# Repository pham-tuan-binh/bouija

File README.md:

# Bouija

A PCB business card that runs an LLM locally with an Ouija board-inspired LED layout.

Watch a video on the design of this business card [here](https://youtu.be/WC3O2cKT8Eo).

**Special thanks to NextPB for sponsoring this project. Check out their website [here](https://www.nextpcb.com?code=Build_With_Binh)**

## Overview

Bouija is a unique business card featuring an ESP32-S3 that runs a local Large Language Model. The device uses 40 individually addressable WS2812B LEDs arranged in an Ouija board pattern to visualize text generation in real-time.

## Specifications

- **PCB Dimensions**: 85mm × 54mm with 3mm corner radius
- **LEDs**: 40 WS2812B LEDs
  - 26 letters (A-Z)
  - 10 numbers (0-9)
  - 4 shortcuts: cap, slap, peace, sup
- **MCU**: ESP32-S3 with 8MB PSRAM and 16MB Flash
- **Layout**: Ouija board arrangement for cultural authenticity

## Firmware Options

### Simple Mode (`/firmware/simple`)

Hard-coded messages with LED visualization and touch interaction.

### LLM Mode (`/firmware/tinyllama`)

Local LLM text generation using [Dave Bennett's ESP32 LLM implementation](https://github.com/DaveBben/esp32-llm). Credit to Dave Bennett for the LLM core - I added the visualization and interaction layer.

## Setup

Requires ESP-IDF toolchain:

```bash
# Navigate to desired firmware directory
cd firmware/tinyllama  # or firmware/simple

# Build and flash
idf.py build
idf.py -p /dev/{DEVICE_PORT} flash
```

## Hardware

The PCB design is available in `/pcb` as a KiCad project.

## Why "Bouija"?

It's a play on "Ouija" + "Binh" (the creator's name) - because what's a business card without a little wordplay? 👻

---

_Running AI on a business card because why not?_

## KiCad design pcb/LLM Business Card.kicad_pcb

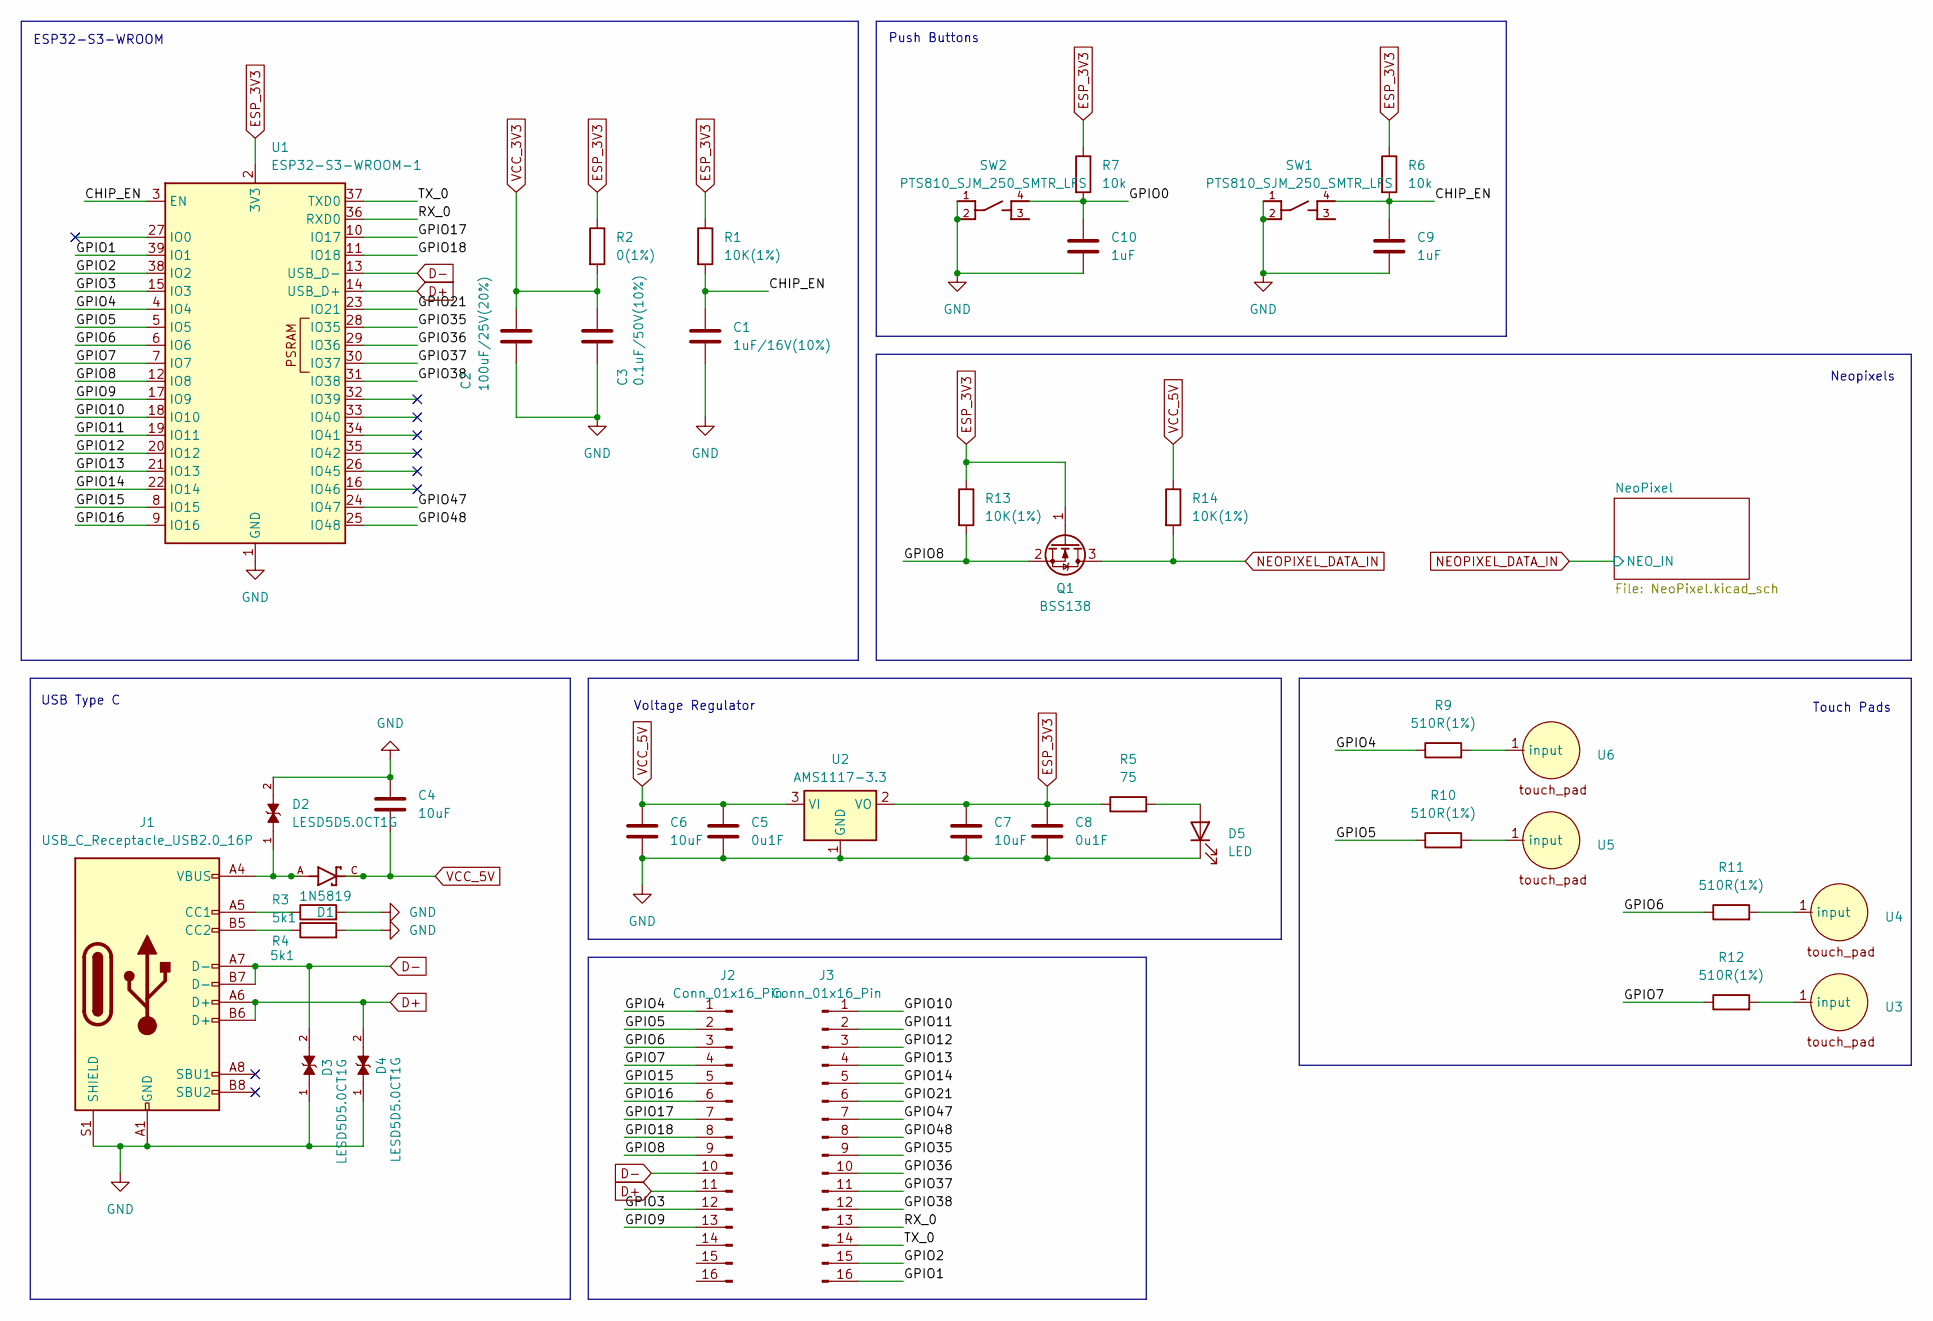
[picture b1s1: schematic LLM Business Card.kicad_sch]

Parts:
C1: 1uF/16V(10%); C_0805_2012Metric
C2: 100uF/25V(20%); C_0805_2012Metric
C3: 0.1uF/50V(10%); C_0805_2012Metric
C4, C6, C7: 10uF; C_0805_2012Metric
C5, C8: 0u1F; C_0805_2012Metric
C9, C10: 1uF; C_0805_2012Metric
D1: 1N5819; SOD3715X145N; PARTREV 18-2
D2, D3, D4: LESD5D5.0CT1G; TVS_LESD5D5.0CT1G; PARTREV O
D5: LED; LED_0402_1005Metric_Pad0.77x0.64mm_HandSolder
J1: USB_C_Receptacle_USB2.0_16P; USB_C_Receptacle_GCT_USB4105-xx-A_16P_TopMnt_Horizontal
J2, J3: Conn_01x16_Pin; PinSocket_1x16_P2.54mm_Vertical
Q1: BSS138; SOT-23
R1, R13, R14: 10K(1%); R_0402_1005Metric_Pad0.72x0.64mm_HandSolder
R2: 0(1%); R_0402_1005Metric_Pad0.72x0.64mm_HandSolder
R3, R4: 5k1; R_0402_1005Metric_Pad0.72x0.64mm_HandSolder
R5: 75; R_0402_1005Metric_Pad0.72x0.64mm_HandSolder
R6, R7: 10k; R_0402_1005Metric_Pad0.72x0.64mm_HandSolder
R9, R10, R11, R12: 510R(1%); R_0402_1005Metric_Pad0.72x0.64mm_HandSolder
SW1, SW2: PTS810_SJM_250_SMTR_LFS; SW_PTS810_SJM_250_SMTR_LFS
U1: ESP32-S3-WROOM-1
U2: AMS1117-3.3; SOT-223-3_TabPin2
U3, U4, U5, U6: TouchPad

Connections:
/CHIP_EN: C1.1, C9.1, R1.2, R6.2, SW1.4, U1.3 (EN)
/GPIO0: C10.1, R7.2, SW2.4
/GPIO1: J3.16, U1.39 (IO1)
/GPIO2: J3.15, U1.38 (IO2)
/GPIO3: J2.12, U1.15 (IO3)
/GPIO4: J2.1, R9.1, U1.4 (IO4)
/GPIO5: J2.2, R10.1, U1.5 (IO5)
/GPIO6: J2.3, R11.1, U1.6 (IO6)
/GPIO7: J2.4, R12.1, U1.7 (IO7)
/GPIO8: J2.9, Q1.2 (S), R13.2, U1.12 (IO8)
/GPIO9: J2.13, U1.17 (IO9)
/GPIO10: J3.1, U1.18 (IO10)
/GPIO11: J3.2, U1.19 (IO11)
/GPIO12: J3.3, U1.20 (IO12)
/GPIO13: J3.4, U1.21 (IO13)
/GPIO14: J3.5, U1.22 (IO14)
/GPIO15: J2.5, U1.8 (IO15)
/GPIO16: J2.6, U1.9 (IO16)
/GPIO17: J2.7, U1.10 (IO17)
/GPIO18: J2.8, U1.11 (IO18)
/GPIO21: J3.6, U1.23 (IO21)
/GPIO35: J3.9, U1.28 (IO35)
/GPIO36: J3.10, U1.29 (IO36)
/GPIO37: J3.11, U1.30 (IO37)
/GPIO38: J3.12, U1.31 (IO38)
/GPIO47: J3.7, U1.24 (IO47)
/GPIO48: J3.8, U1.25 (IO48)
/RX_0: J3.13, U1.36 (RXD0)
/TX_0: J3.14, U1.37 (TXD0)
D+: D4.2, J1.A6 (D+), J1.B6 (D+), J2.11, U1.14 (USB_D+)
D-: D3.2, J1.A7 (D-), J1.B7 (D-), J2.10, U1.13 (USB_D-)
ESP_3V3: C7.1, C8.1, Q1.1 (G), R1.1, R2.1, R5.1, R6.1, R7.1, R13.1, U1.2 (3V3), U2.2 (VO)
GND: C1.2, C2.2, C3.2, C4.1, C5.2, C6.2, C7.2, C8.2, C9.2, C10.2, D2.2, D3.1, D4.1, D5.1 (K), J1.A1 (GND), J1.A12 (GND), J1.B1 (GND), J1.B12 (GND), J1.S1 (SHIELD), R3.2, R4.2, SW1.1, SW1.2, SW2.1, SW2.2, U1.1 (GND), U1.40 (GND), U1.41 (GND), U2.1 (GND); also elsewhere on the board
NEOPIXEL_DATA_IN: Q1.3 (D), R14.2; also elsewhere on the board
unnamed: D1.A, D2.1, J1.A4 (VBUS), J1.A9 (VBUS), J1.B4 (VBUS), J1.B9 (VBUS)
unnamed: D5.2 (A), R5.2
unnamed: J1.A5 (CC1), R3.1
unnamed: J1.B5 (CC2), R4.1
unnamed: R12.2, U3.1 (input)
unnamed: R11.2, U4.1 (input)
unnamed: R10.2, U5.1 (input)
unnamed: R9.2, U6.1 (input)
VCC_3V3: C2.1, C3.1, R2.2
VCC_5V: C4.2, C5.1, C6.1, D1.C, R14.1, U2.3 (VI); also elsewhere on the board

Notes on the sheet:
Push Buttons
Touch Pads
Voltage Regulator
Neopixels
USB Type C
ESP32-S3-WROOM

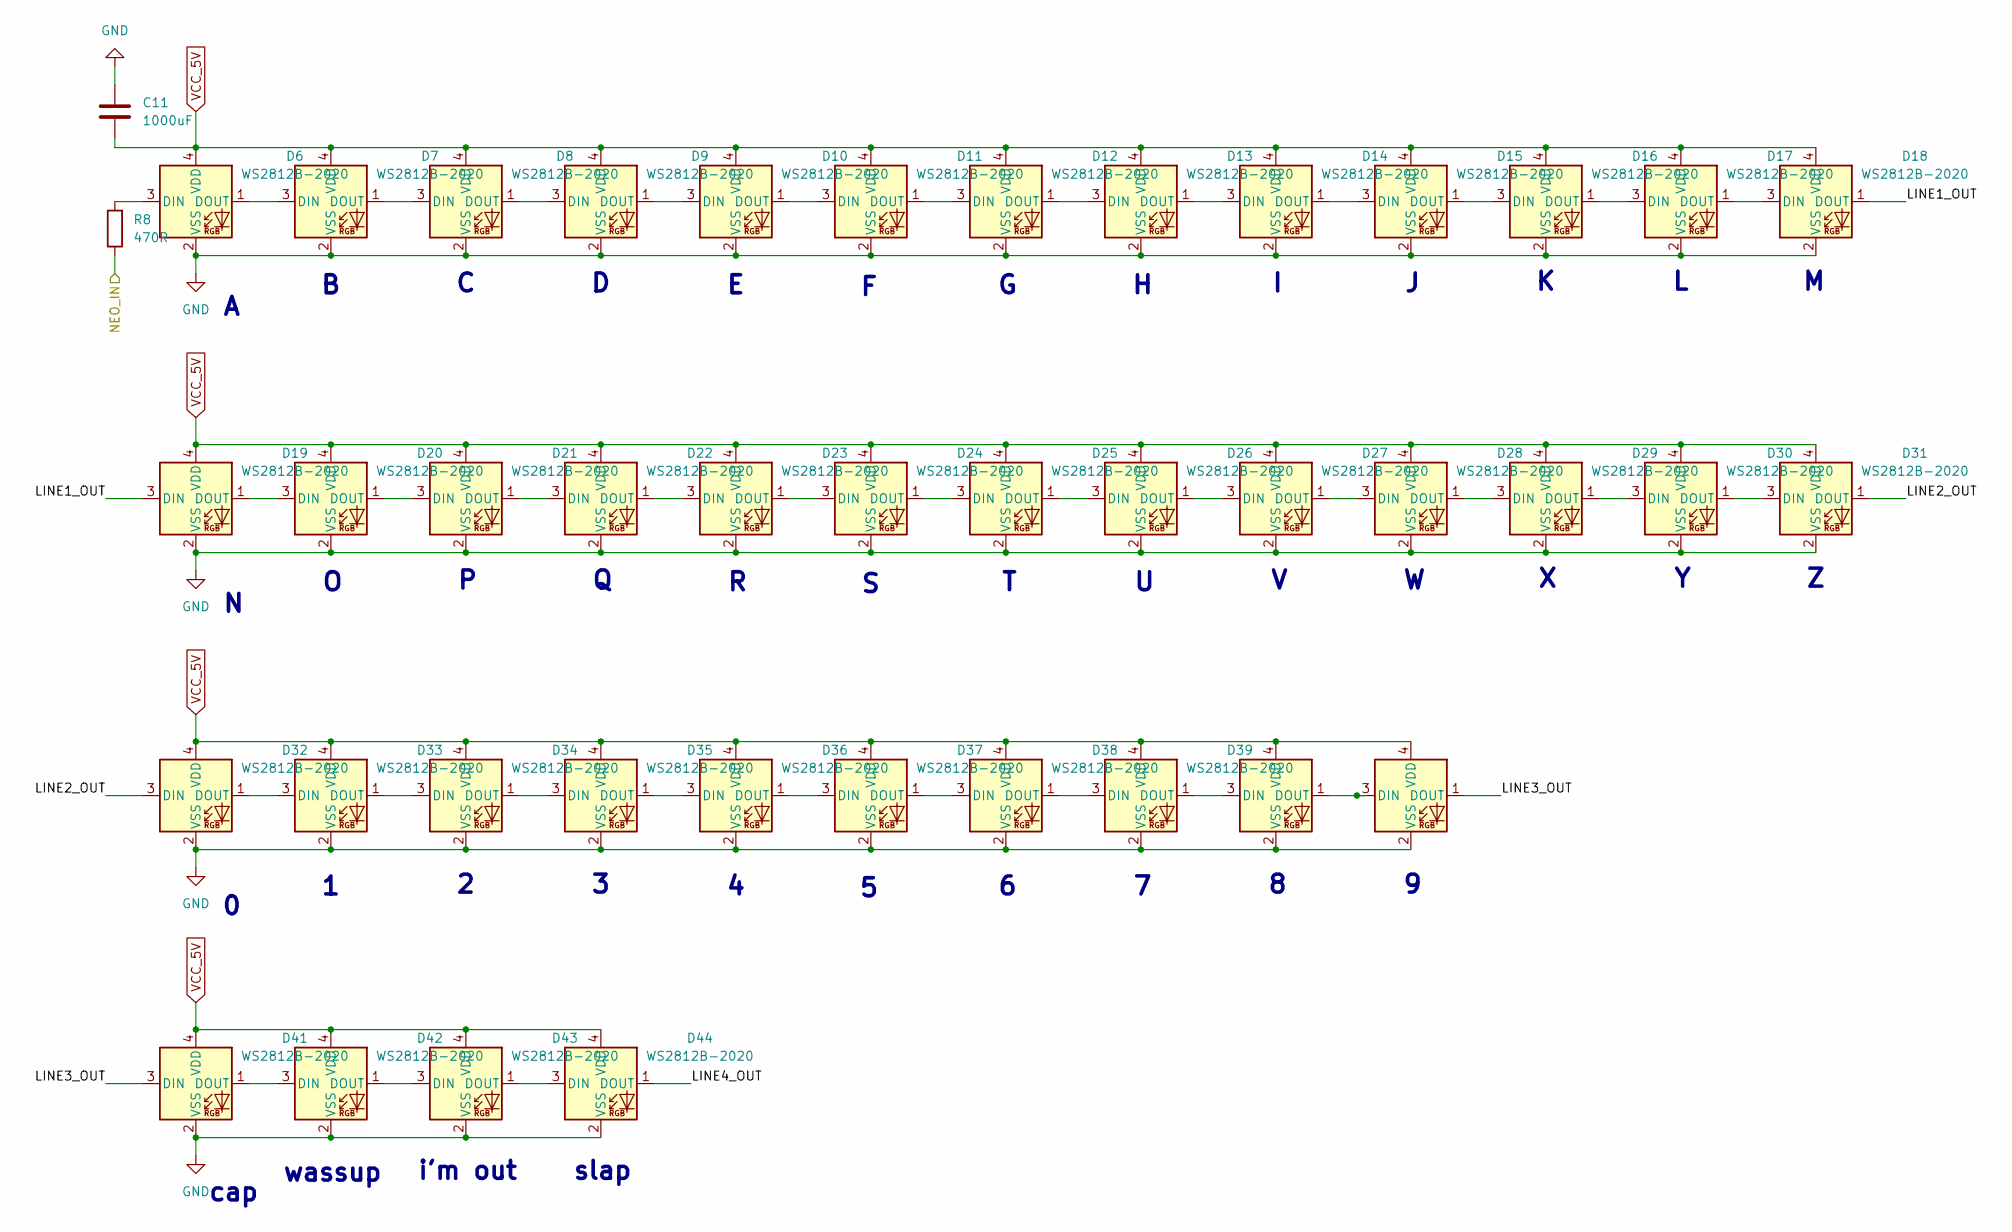
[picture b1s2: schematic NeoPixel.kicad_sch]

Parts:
C11: 1000uF; C_0805_2012Metric
D6, D7, D8, D9, D10, D11, D12, D13, D14, D15, D16, D17, D18, D19, D20, D21, D22, D23, D24, D25, D26, D27, D28, D29, D30, D31, D32, D33, D34, D35, D36, D37, D38, D39, D40, D41, D42, D43, D44, D46: WS2812B-2020; LED_WS2812B-2020_PLCC4_2.0x2.0mm
R8: 470R; R_0402_1005Metric_Pad0.72x0.64mm_HandSolder

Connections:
/NeoPixel/LINE1_OUT: D18.1 (DOUT), D19.3 (DIN)
/NeoPixel/LINE2_OUT: D31.1 (DOUT), D32.3 (DIN)
/NeoPixel/LINE3_OUT: D41.3 (DIN), D46.1 (DOUT)
/NeoPixel/LINE4_OUT: D44.1 (DOUT)
GND: C11.1, D6.2 (VSS), D7.2 (VSS), D8.2 (VSS), D9.2 (VSS), D10.2 (VSS), D11.2 (VSS), D12.2 (VSS), D13.2 (VSS), D14.2 (VSS), D15.2 (VSS), D16.2 (VSS), D17.2 (VSS), D18.2 (VSS), D19.2 (VSS), D20.2 (VSS), D21.2 (VSS), D22.2 (VSS), D23.2 (VSS), D24.2 (VSS), D25.2 (VSS), D26.2 (VSS), D27.2 (VSS), D28.2 (VSS), D29.2 (VSS), D30.2 (VSS), D31.2 (VSS), D32.2 (VSS), D33.2 (VSS), D34.2 (VSS), D35.2 (VSS), D36.2 (VSS), D37.2 (VSS), D38.2 (VSS), D39.2 (VSS), D40.2 (VSS), D41.2 (VSS), D42.2 (VSS), D43.2 (VSS), D44.2 (VSS), D46.2 (VSS); also elsewhere on the board
NEOPIXEL_DATA_IN: R8.1; also elsewhere on the board
unnamed: D6.3 (DIN), R8.2
unnamed: D6.1 (DOUT), D7.3 (DIN)
unnamed: D7.1 (DOUT), D8.3 (DIN)
unnamed: D8.1 (DOUT), D9.3 (DIN)
unnamed: D9.1 (DOUT), D10.3 (DIN)
unnamed: D10.1 (DOUT), D11.3 (DIN)
unnamed: D11.1 (DOUT), D12.3 (DIN)
unnamed: D12.1 (DOUT), D13.3 (DIN)
unnamed: D13.1 (DOUT), D14.3 (DIN)
unnamed: D14.1 (DOUT), D15.3 (DIN)
unnamed: D15.1 (DOUT), D16.3 (DIN)
unnamed: D16.1 (DOUT), D17.3 (DIN)
unnamed: D17.1 (DOUT), D18.3 (DIN)
unnamed: D19.1 (DOUT), D20.3 (DIN)
unnamed: D20.1 (DOUT), D21.3 (DIN)
unnamed: D21.1 (DOUT), D22.3 (DIN)
unnamed: D22.1 (DOUT), D23.3 (DIN)
unnamed: D23.1 (DOUT), D24.3 (DIN)
unnamed: D24.1 (DOUT), D25.3 (DIN)
unnamed: D25.1 (DOUT), D26.3 (DIN)
unnamed: D26.1 (DOUT), D27.3 (DIN)
unnamed: D27.1 (DOUT), D28.3 (DIN)
unnamed: D28.1 (DOUT), D29.3 (DIN)
unnamed: D29.1 (DOUT), D30.3 (DIN)
unnamed: D30.1 (DOUT), D31.3 (DIN)
unnamed: D32.1 (DOUT), D33.3 (DIN)
unnamed: D33.1 (DOUT), D34.3 (DIN)
unnamed: D34.1 (DOUT), D35.3 (DIN)
unnamed: D35.1 (DOUT), D36.3 (DIN)
unnamed: D36.1 (DOUT), D37.3 (DIN)
unnamed: D37.1 (DOUT), D38.3 (DIN)
unnamed: D38.1 (DOUT), D39.3 (DIN)
unnamed: D39.1 (DOUT), D40.3 (DIN)
unnamed: D40.1 (DOUT), D46.3 (DIN)
unnamed: D41.1 (DOUT), D42.3 (DIN)
unnamed: D42.1 (DOUT), D43.3 (DIN)
unnamed: D43.1 (DOUT), D44.3 (DIN)
VCC_5V: C11.2, D6.4 (VDD), D7.4 (VDD), D8.4 (VDD), D9.4 (VDD), D10.4 (VDD), D11.4 (VDD), D12.4 (VDD), D13.4 (VDD), D14.4 (VDD), D15.4 (VDD), D16.4 (VDD), D17.4 (VDD), D18.4 (VDD), D19.4 (VDD), D20.4 (VDD), D21.4 (VDD), D22.4 (VDD), D23.4 (VDD), D24.4 (VDD), D25.4 (VDD), D26.4 (VDD), D27.4 (VDD), D28.4 (VDD), D29.4 (VDD), D30.4 (VDD), D31.4 (VDD), D32.4 (VDD), D33.4 (VDD), D34.4 (VDD), D35.4 (VDD), D36.4 (VDD), D37.4 (VDD), D38.4 (VDD), D39.4 (VDD), D40.4 (VDD), D41.4 (VDD), D42.4 (VDD), D43.4 (VDD), D44.4 (VDD), D46.4 (VDD); also elsewhere on the board

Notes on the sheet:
i'm out
wassup
cap
slap

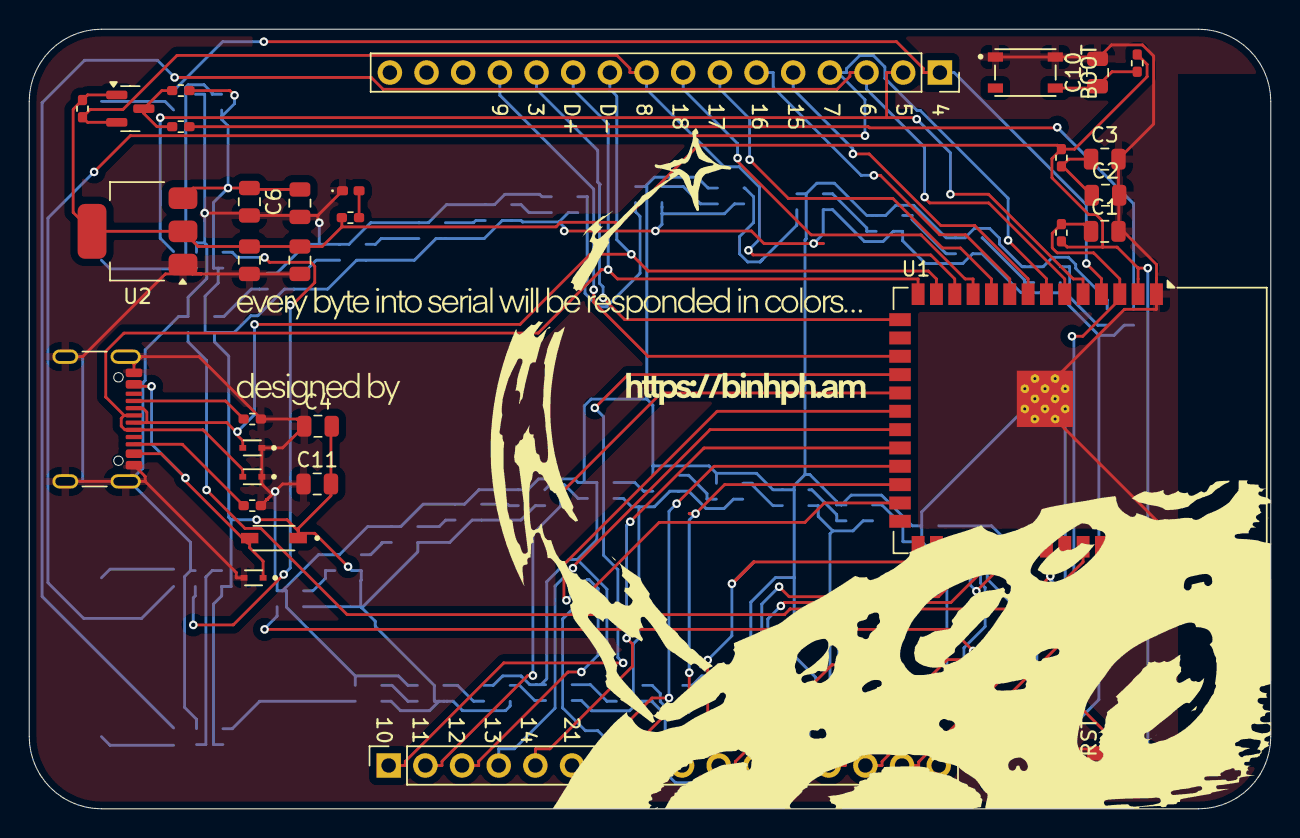
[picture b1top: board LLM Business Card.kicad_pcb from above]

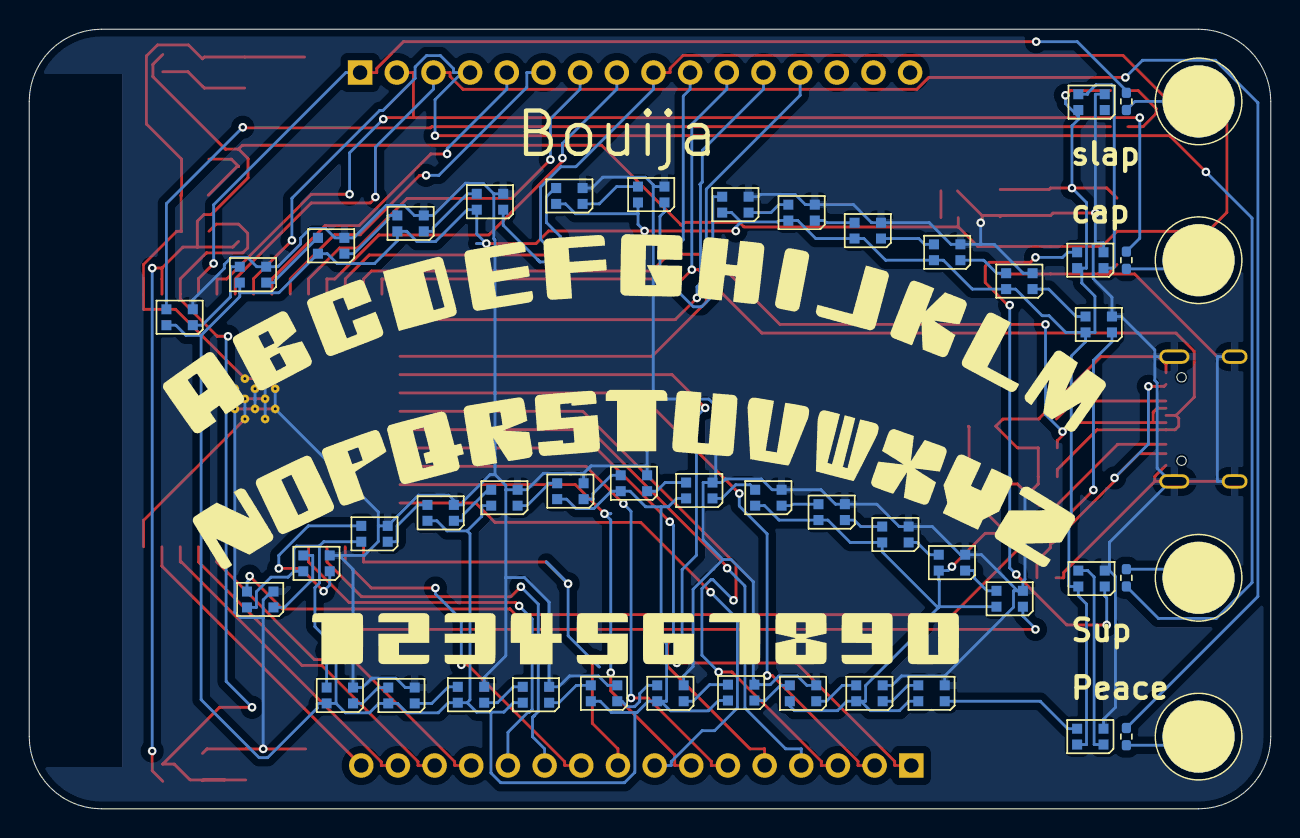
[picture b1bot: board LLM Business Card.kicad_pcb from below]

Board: 2 copper layers, 86.0 x 54.0 mm, 84 parts (49 on the bottom side), 84 nets.

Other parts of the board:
Moon: LOGO; FrontSilk
Ouija: LOGO; Ouija

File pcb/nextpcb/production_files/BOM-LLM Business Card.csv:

MPN,Qty,Designator,value,manufacturer,Category,SKU,Customer Supply,Customer Remark
FS21X105K160ECG,3,"C1,C9,C10",1uF/16V(10%),Pitts Sales Associates (PSA),Capacitors,2500360793
GRM21BR60J107ME15L,1,C2,100uF/25V(20%),Murata,Ceramic Capacitors,1103483307
C0805C104K5RAC7215,1,C3,0.1uF/50V(10%),Yageo,Ceramic Capacitors,-
EMK212BB7106KG-T,3,"C6,C4,C7",10uF,Taiyo Yuden,Capacitors,1104534147
0805ZC104MAT2A,2,"C8,C5",0u1F,Kyocera,Ceramic Capacitors,1012110635
EEUFC1E102,1,C11,1000uF,Panasonic,Aluminum Electrolytic Capacitors,1033725480
1N5819,1,D1,1N5819,Vishay,Schottky Diodes,1100180393
LESD5D5.0CT1G,3,"D4,D3,D2",LESD5D5.0CT1G,Leshan Radio Company (LRC),TVS Diodes,2500314833
ALED7707TR,1,D5,LED,STMicroelectronics,LED Drivers,1104102559
WS2812B-2020,40,"D14,D25,D30,D39,D38,D34,D12,D13,D28,D44,D36,D15,D26,D10,D32,D9,D6,D20,D35,D8,D7,D31,D29,D17,D43,D46,D18,D19,D27,D37,D24,D42,D33,D22,D40,D23,D21,D41,D16,D11",WS2812B-2020,WORLDSEMI,LEDs,2500385105
TYPE-C16PIN,1,J1,USB_C_Receptacle_USB2.0_16P,SHOU HAN,USB Connectors,2500412404
,2,"J2,J3",Conn_01x16_Pin,,,
BSS138,1,Q1,BSS138,Hottech,MOSFETs,1112375387
PESD0542U005,1,R2,0(1%),Leiditech,TVS Diodes,1019351440
CRCW04025K10FKED,2,"R3,R4",5k1,Vishay,Chip SMD Resistors,1101330961
PESD0402AV12,1,R5,75,Leiditech,TVS Diodes,1023216890
RC0402JR-0710KL,2,"R7,R6",10k,Yageo,Chip SMD Resistors,1101287477
AC0402FR-07470RL,1,R8,470R,Yageo,Chip SMD Resistors,1103497035
RK73H1ETTP5100F,4,"R12,R10,R9,R11",510R(1%),KOA,Chip SMD Resistors,1105758435
RK73H1ERTTP1002F,3,"R14,R13,R1",10K(1%),KOA,Chip SMD Resistors,1111269901
PTS810SJM250SMTRLFS,2,"SW1,SW2",PTS810_SJM_250_SMTR_LFS,C&K SYSTEMS,Tactile Switches,2500325932
ESP32-S3-WROOM-1-N16R8,1,U1,ESP32-S3-WROOM-1,Espressif Systems,WiFi Modules,1112149751
AMS1117-3.3,1,U2,AMS1117-3.3,JSMICRO,"Linear Voltage Regulators, LDO",2500288463
,4,"U4,U5,U6,U3",~,,,

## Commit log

2025-09-05 First
2025-09-05 Magic 8 ball
2025-09-06 Added README
2025-09-08 Add sponsorship acknowledgment for NextPB
    Added a special thanks section for NextPB sponsorship.
